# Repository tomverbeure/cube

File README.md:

# LED Cube with Cisco Controller and Pixel Purse LED Panels

This repo needs a bit of cleanup for general public consumption,
but it had all the assets for my LED cube that’s built from
[Project MC2 Pixel Purse LED panels](https://tomverbeure.github.io/2019/10/03/Pixel-Purse.html) 
and a [Cisco HWIC-3G-CDMA modem](https://tomverbeure.github.io/2019/11/11/Cisco-HWIC-3G-CDMA.html).

I gave a talk about this project at BangBangCon West 2020: here are
the [video](https://www.youtube.com/watch?v=0tBU5-lJYmU) and [slides](https://docs.google.com/presentation/d/1FYmVh-brx6SpZoJmzuIXrNegWdtriQ9k38EbrvDupg8) of the talk.

I also wrote a [blog post](https://tomverbeure.github.io/2021/05/16/Pixel-Purse-LED-Cube.html)
about this project.

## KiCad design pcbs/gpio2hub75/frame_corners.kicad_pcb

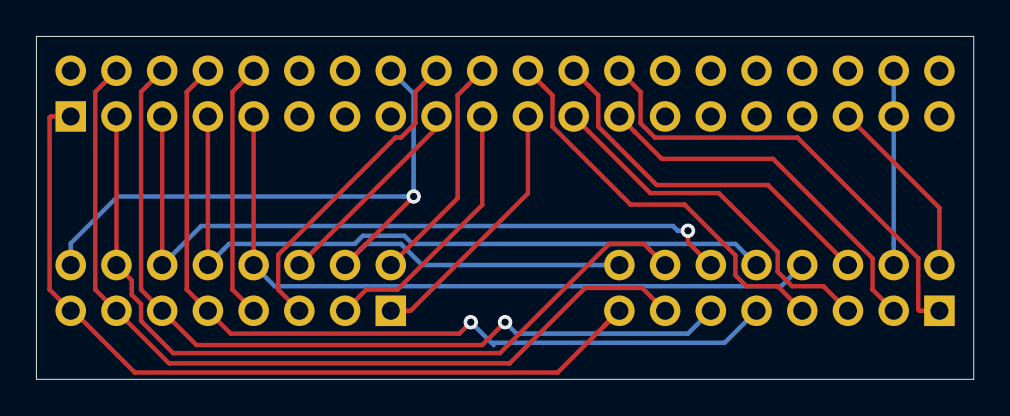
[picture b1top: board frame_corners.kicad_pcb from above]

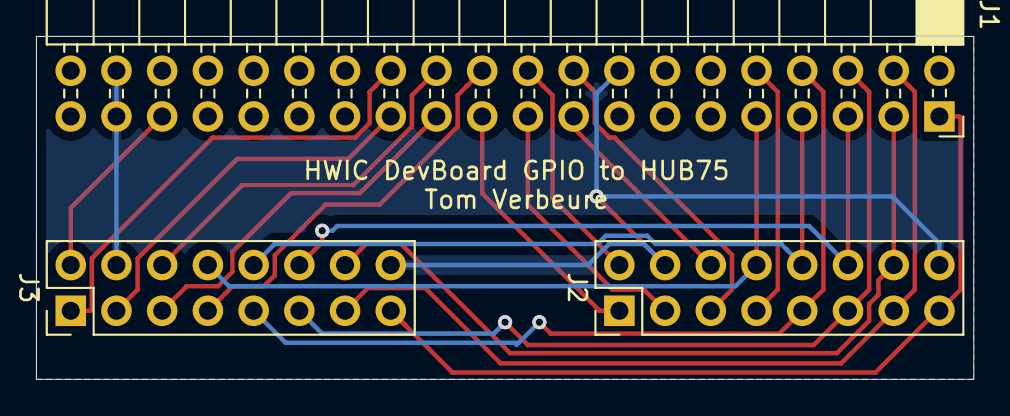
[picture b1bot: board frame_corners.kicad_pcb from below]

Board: 2 copper layers, 52.1 x 19.1 mm, 3 parts (3 on the bottom side), 21 nets.

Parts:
J1: Conn_02x20_Odd_Even; PinSocket_2x20_P2.54mm_Horizontal
J2, J3: Conn_02x08_Odd_Even; PinHeader_2x08_P2.54mm_Vertical

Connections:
/A: J1.8, J2.9, J3.9
/B: J1.7, J2.10, J3.10
/B1: J1.19, J2.3
/B2: J1.10, J2.7
/B3: J1.25, J3.3
/B4: J1.22, J3.7
/C: J1.6, J2.11, J3.11
/CLK: J1.4, J2.13, J3.13
/D: J1.5, J2.12, J3.12
/E: J1.9, J2.8, J3.8
/G1: J1.20, J2.2
/G2: J1.17, J2.6
/G3: J1.35, J3.2
/G4: J1.24, J3.6
/LAT: J1.3, J2.14, J3.14
/OE_: J1.1, J2.15, J3.15
/PD1: J1.18, J2.5
/PD4: J1.21, J2.1
/PD6: J1.23, J3.5
/PF0: J1.26, J3.1
GND: J1.16, J1.37, J1.38, J2.4, J2.16, J3.4, J3.16

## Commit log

2019-12-09 Creation.
2019-12-09 Add VexRiscv as submodule.
2019-12-09 Small system from LedMatrix project.
2019-12-09 Fix code location mistake.
2019-12-09 Add missing ./project files.
2019-12-09 Minimal SW environment.
2019-12-09 Ignore compilation results.
2019-12-09 Add TB.
2019-12-09 LedMatrix -> Cube
2019-12-13 Hub75Drv checkpoint.
2019-12-27 First moving image.
2019-12-27 Fix incorrect one row offset.
2019-12-29 Expand columns past 64 for chained panels.
2019-12-29 Clean blanking, longer LAT pulse.
    Increase column scanning phase by 3 clock cycles so that BLANK/OE_
    and LAT can be switched on and off in their own clock cycles for
    a clean image.
2019-12-29 Minor cleanup.
2019-12-29 hub75Config -> conf. Moving pattern (with artifacts...)
2019-12-29 Flip bit_cntr and row_cntr update. Ghosting is gone.
2019-12-29 Just make LEDs blink again to prove that CPU is working.
2019-12-29 Rick.
2019-12-30 Add dmaBus to main arbiter.
2019-12-30 4KB -> 32KB of CPU memory.
2019-12-30 Separate Hub75 driver from Hub75 pixel generator.
2019-12-30 Add Buffer FIFO between Hub75 streamer and phy.
2019-12-30 Move dmaApb bus to Hub75 streamer.
2019-12-30 Issue DMA request. WIP.
2019-12-31 APB DMA FSM. WIP.
2019-12-31 Conversion to Briey-like SOC. WIP.
2020-01-01 DMA streamer. WIP.
2020-01-01 Working version with devboard rev 2.
2020-01-02 Move LedMem to CubeTop. WIP.
2020-01-02 Wire up LedMem to Hub75Streamer.
2020-01-02 Stream LED data from RAM.
2020-01-02 Fill up Ram with test pattern.
2020-01-03 Refactor panel information.
2020-01-03 Fixes for new panel_cntr.
2020-01-03 Fix a few more panel_cntr related issues.
2020-01-05 Fix address fetch calculation.
2020-01-05 Shorting sim time. Improve TB.
2020-01-05 Double buffered LedMem.
2020-01-05 Control Hub75Streamer via registers.
2020-01-05 Beef up CPU.
2020-01-05 Create 8bpp rick.
2020-01-05 Animated rick on LED. Looks terrible...
2020-01-05 Generate .png files cleaner.
2020-01-05 Rick with paletted colors.
2020-01-05 Alternative rick.
2020-01-08 Use PLL to create 50 MHz clock.
2020-01-08 Minor stuff.
2020-01-08 Fix Quartus update_ram.
2020-01-10 frame_corners checkpoint.
2020-01-11 mechanical -> pcbs
2020-01-11 Remove GPIO 2 HUB75 board from frame corners.
2020-01-11 First version
2020-01-11 Minor changes.
2020-01-12 gpio2hub75 board
2020-01-12 Changed clock names.
2020-01-12 Add Cyclone2 PLL.
2020-01-12 Use true-dual ported Altera memory for synthesis generation.
2020-01-13 Panelization with https://gitlab.com/dren.dk/kicad-util
2020-01-16 Fix bit extraction from APB write.
2020-01-16 Move gamma correction from SW to HW.
2020-01-16 Don't pipeline iBus.
2020-01-16 Move towards SW LED renderer.
2020-01-19 Different panel orientation per side.
2020-01-20 Lower refresh rate and bpc to avoid signal integrity issues.
2020-01-23 Drive 2 parallel HUB75 interfaces.
2020-01-23 Make panel parameters programmable
2020-01-23 Start configuration panel info registers.
2020-01-24 Add frame counter.
2020-01-24 Use frame counter.
2020-01-24 Rick is rolling again.
2020-01-24 Fix panel info for right connector panels.
2020-01-24 Fix one more panel.
2020-01-25 Fix GCC warning.
2020-01-25 4x RGB instead of 2x.
2020-01-25 Latest waves.
2020-01-25 Switch back to 120Hz.
2020-01-25 Fix orientation of all faces!
2020-01-25 Power measurements.
2020-01-25 Add global dimming.
2020-01-25 Different sides read from different led_mem.
2020-01-26 Minor refactoring.
2020-01-26 Enable RV32 compression.
2020-01-26 Pacmans are paccing.
2020-01-27 Fix one side for back-to-bottom overflow.
2020-01-27 Ghosts.
2020-01-27 Add more Pacman stuff.
2020-01-27 Separate Rick and pacman.
2020-01-27 Reduce Rick to 16 colors.
2020-01-27 Rick: store 2 nibbles in 1 byte to save 50% storage.
2020-01-27 Rotate between Rick and pacman.
2020-01-27 Add Mario.
2020-02-29 Demo bitstream.
2020-03-01 Speech WIP.
2023-11-03 More robust palette.info parser.
